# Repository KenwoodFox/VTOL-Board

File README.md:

# VTOL-Board

The board and firmware for the EG-310 VTOL project.

## Instructions to include this in your own project repo

I recommend using git submodules, add this to your tree like this

```shell
cd my_project
git submodule add https://github.com/KenwoodFox/VTOL-Board
git add -A
git commit -m "Added VTOL board
```

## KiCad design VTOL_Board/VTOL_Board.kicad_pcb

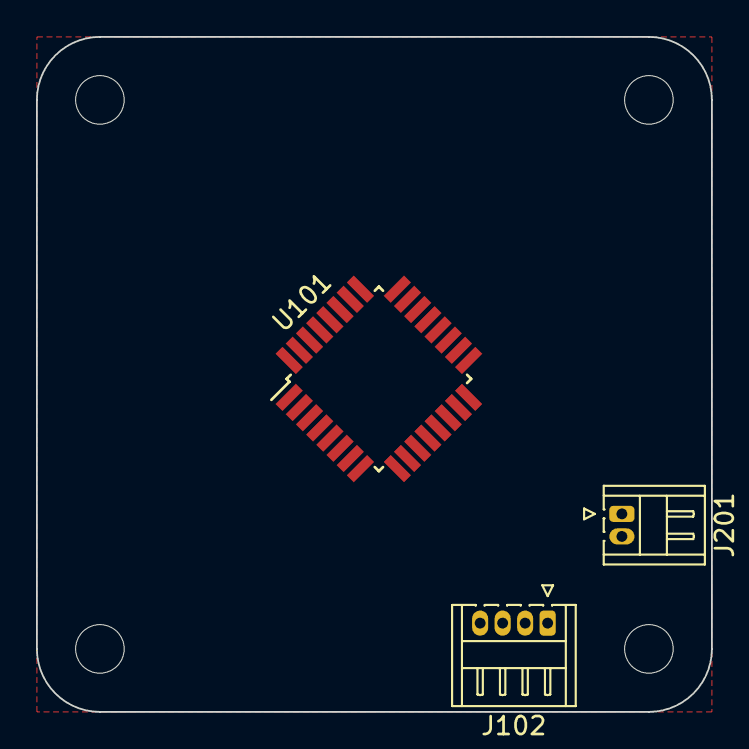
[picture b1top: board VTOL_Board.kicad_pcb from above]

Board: 2 copper layers, 37.5 x 37.5 mm, 8 parts (0 on the bottom side), 2 nets, no tracks yet.

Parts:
H102, H103, H105, H106: PiMountingHole; MountingHole_2.7mm
J102: Servo1; Hirose_DF13-04P-1.25DS_1x04_P1.25mm_Horizontal
J201: PWR In; Hirose_DF13-02P-1.25DS_1x02_P1.25mm_Horizontal
SNHU_NEW***: LOGO; SNHU_NEW
U101: ATmega328P; TQFP-32_7x7mm_P0.8mm

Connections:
+5V: U101.4 (VCC), U101.6 (VCC), U101.18 (AVCC)
GND: J201.2, U101.3 (GND), U101.5 (GND), U101.21 (GND)

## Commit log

2023-01-10 Add all from pendulum328
2023-01-10 Modify boilerplate for vtol
2023-01-10 Bump
2023-01-10 Use small hirose connectors
2023-01-10 Fixup!
2023-01-25 Change MCU
